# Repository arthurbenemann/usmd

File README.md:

# uSMD

## Board

## BOM
|Qty.|Rec. Qty.|DK Part Number     |Manufacturer Part Number|Description                    |Reference                      |Unit Price|Extended Price|
|----|--------|---------------------------|------------------------|-------------------------------|-------------------------------|----------|--------------|
|10  |15      |587-4850-1-ND              |JMK021BJ103KK5W         |CAP CER 10000PF 6.3V X5R 008004|C1 - C10                       |0.53300   |$8.00         |
|1   |2       |754-2028-1-ND              |APG0603SEC-E-TT         |LED RED CLEAR 2SMD             |D1                             |0.43000   |$0.86         |
|1   |3       |118-CR01005-FW-1001GLFCT-ND|CR01005-FW-1001GLF      |RES 1K OHM 1% 1/32W 01005      |R1                             |0.10000   |$0.30         |
|1   |3       |YAG6214CT-ND               |RC0100FR-0710ML         |RES SMD 10M OHM 1% 1/32W 01005 |R2                             |0.31000   |$0.93         |
|1   |2       |296-46430-1-ND             |LMC555CTPX/NOPB         |IC OSC SINGLE TIMER 3MHZ 8-USMD|U1                             |1.34000   |$2.68         |
|1   |1       |36-3031-ND                 |3031                    |BATTERY RETAINER COIN PC PIN   |BT1                            |0.61000   |$0.61         |
|1   |1       |P031-ND                    |CR-1025/BN              |BATTERY LITHIUM 3V COIN 10MM   |N/A                            |1.03000   |$1.03         |
|1   |3       |[6NPtd21R](https://oshpark.com/shared_projects/6NPtd21R)|uSMD-Rev1-PCB|uSMD OSHPARK PCB|N/A                         |0.50000   |$1.50         |
|    |        |                           |                        |                               |                               |**Total** |**$15.64**    |

## Photos
uSMD and [misery challenge](https://github.com/aspro648/KiCad/tree/master/projects/Attiny/AttinyChallengeMisery) stacked up.

USMD under microscope

Size of an 08004 against a human hair

If all compoents are soldered properly LED should blink at ~1Hz:

## External
Marco Reps assembly on video, better than the original: https://www.youtube.com/watch?v=2vpTYaDGmCs&t=1451s

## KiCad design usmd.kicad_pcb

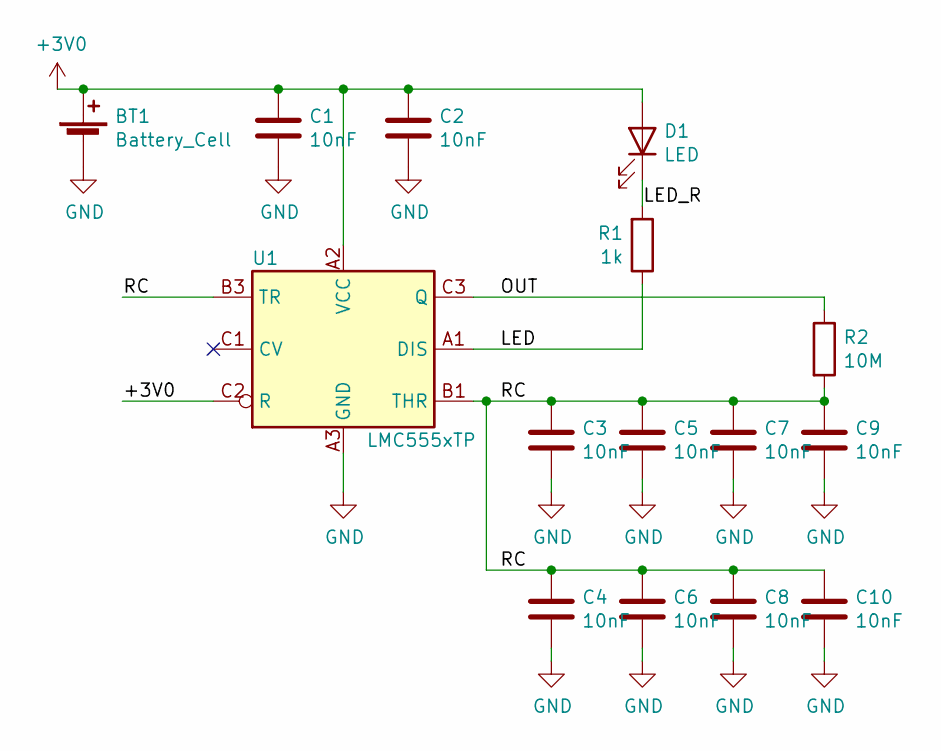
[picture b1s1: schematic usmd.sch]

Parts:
BT1: Battery_Cell; BatteryHolder_Keystone_3031_1x10mm; MPN 3031
C1, C2, C3, C4, C5, C6, C7, C8, C9, C10: 10nF; C_008004_0201Metric; MPN 587-4850-1-ND
D1: LED; LED_0201_0603Metric; MPN APG0603SEC-E-TT
R1: 1k; R_01005_0402Metric; MPN CR01005-FW-1001GLF
R2: 10M; R_01005_0402Metric; MPN ‎YAG6214CT-ND‎
U1: LMC555xTP; Texas_DSBGA-8_1.43x1.41mm_Layout3x3_P0.5mm; MPN LMC555CTPX/NOPB

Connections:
+3V0: BT1.1 (+), C1.1, C2.1, D1.2 (A), U1.A2 (VCC), U1.C2 (R)
/LED: R1.1, U1.A1 (DIS)
/LED_R: D1.1 (K), R1.2
/OUT: R2.1, U1.C3 (Q)
/RC: C3.1, C4.1, C5.1, C6.1, C7.1, C8.1, C9.1, C10.1, R2.2, U1.B1 (THR), U1.B3 (TR)
GND: BT1.2 (-), C1.2, C2.2, C3.2, C4.2, C5.2, C6.2, C7.2, C8.2, C9.2, C10.2, U1.A3 (GND)

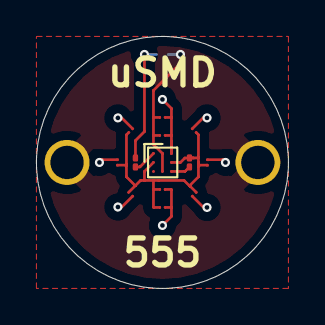
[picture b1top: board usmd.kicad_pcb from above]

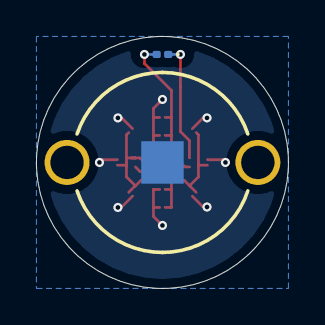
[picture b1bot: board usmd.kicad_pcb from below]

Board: 2 copper layers, 14.0 x 14.0 mm, 15 parts (2 on the bottom side), 6 nets.

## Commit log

2021-04-13 Add assembled unit photos
2021-04-13 add pictures to readme
2021-04-13 add LTspice sim
2021-04-13 add simulation to readme
